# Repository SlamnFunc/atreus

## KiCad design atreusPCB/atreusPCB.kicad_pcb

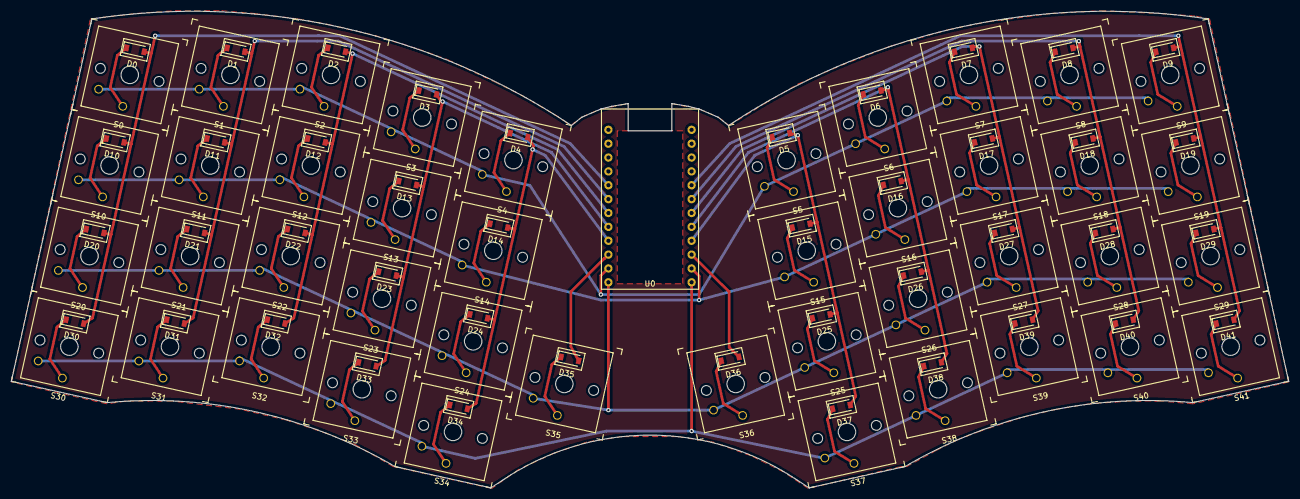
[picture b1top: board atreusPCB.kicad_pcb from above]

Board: 2 copper layers, 234.0 x 87.3 mm, 85 parts (0 on the bottom side), 58 nets.

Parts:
D0, D1, D2, D3, D4, D5, D6, D7, D8, D9, D10, D11, D12, D13, D14, D15, D16, D17, D18, D19, D20, D21, D22, D23, D24, D25, D26, D27, D28, D29, D30, D31, D32, D33, D34, D35, D36, D37, D38, D39, D40, D41: DIODE; D_SOD-123
S0, S1, S2, S3, S4, S5, S6, S7, S8, S9, S10, S11, S12, S13, S14, S15, S16, S17, S18, S19, S20, S21, S22, S23, S24, S25, S26, S27, S28, S29, S30, S31, S32, S33, S34, S35, S36, S37, S38, S39, S40, S41: PG1350; PG1350_diode
U0: ProMicro; ProMicroFlipped

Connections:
C0: D0.2, D10.2, D20.2, D30.2, U0.17
C1: D1.2, D11.2, D21.2, D31.2, U0.18
C2: D2.2, D12.2, D22.2, D32.2, U0.19
C3: D3.2, D13.2, D23.2, D33.2, U0.20
C4: D4.2, D14.2, D24.2, D34.2, U0.21
C5: D35.2, U0.22
C6: D36.2, U0.10
C7: D5.2, D15.2, D25.2, D37.2, U0.9
C8: D6.2, D16.2, D26.2, D38.2, U0.8
C9: D7.2, D17.2, D27.2, D39.2, U0.7
C10: D8.2, D18.2, D28.2, D40.2, U0.6
C11: D9.2, D19.2, D29.2, D41.2, U0.5
unnamed: D0.1, S0.2
unnamed: D1.1, S1.2
unnamed: D2.1, S2.2
unnamed: D3.1, S3.2
unnamed: D4.1, S4.2
unnamed: D5.1, S5.2
unnamed: D6.1, S6.2
unnamed: D7.1, S7.2
unnamed: D8.1, S8.2
unnamed: D9.1, S9.2
unnamed: D10.1, S10.2
unnamed: D11.1, S11.2
unnamed: D12.1, S12.2
unnamed: D13.1, S13.2
unnamed: D14.1, S14.2
unnamed: D15.1, S15.2
unnamed: D16.1, S16.2
unnamed: D17.1, S17.2
unnamed: D18.1, S18.2
unnamed: D19.1, S19.2
unnamed: D20.1, S20.2
unnamed: D21.1, S21.2
unnamed: D22.1, S22.2
unnamed: D23.1, S23.2
unnamed: D24.1, S24.2
unnamed: D25.1, S25.2
unnamed: D26.1, S26.2
unnamed: D27.1, S27.2
unnamed: D28.1, S28.2
unnamed: D29.1, S29.2
unnamed: D30.1, S30.2
unnamed: D31.1, S31.2
unnamed: D32.1, S32.2
unnamed: D33.1, S33.2
unnamed: D34.1, S34.2
unnamed: D35.1, S35.2
unnamed: D36.1, S36.2
unnamed: D37.1, S37.2
unnamed: D38.1, S38.2
unnamed: D39.1, S39.2
unnamed: D40.1, S40.2
unnamed: D41.1, S41.2
R0: S30.1, S31.1, S32.1, S33.1, S34.1, S37.1, S38.1, S39.1, S40.1, S41.1, U0.12
R1: S20.1, S21.1, S22.1, S23.1, S24.1, S25.1, S26.1, S27.1, S28.1, S29.1, S35.1, S36.1, U0.24
R2: S10.1, S11.1, S12.1, S13.1, S14.1, S15.1, S16.1, S17.1, S18.1, S19.1, U0.11
R3: S0.1, S1.1, S2.1, S3.1, S4.1, S5.1, S6.1, S7.1, S8.1, S9.1, U0.23
